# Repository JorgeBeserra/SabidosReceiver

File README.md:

# SabidosReceiver

Projeto de receptor e processador de áudio multicanal baseado no **PT2322-S**, com seletor **PT2323-S**, controlado por um **ESP32**.

## Ferramenta

O projeto principal está em formato **KiCad 10**:

- `SabidosReceiver.kicad_pro`
- `SabidosReceiver.kicad_sch`
- `SabidosReceiver.kicad_pcb`

Abra sempre o arquivo `SabidosReceiver.kicad_pro` para manter o esquemático e a PCB associados ao mesmo projeto.

## Situação da migração

O projeto foi renomeado de `SabVolAudio` para `SabidosReceiver`. Ainda existem arquivos e identificadores legados preservados no repositório para conferência durante a migração.

Antes de removê-los definitivamente, é necessário confirmar que todas as folhas hierárquicas e todos os componentes foram convertidos corretamente para o formato atual do KiCad.

## Cuidados antes da fabricação

1. Confirmar fisicamente o encapsulamento do PT2322-S e validar o footprint em escala 1:1.
2. Abrir e salvar todas as folhas hierárquicas no KiCad 10.
3. Executar o ERC no esquemático.
4. Atualizar a PCB a partir do esquemático e revisar cada inclusão ou remoção proposta.
5. Executar o DRC na PCB.
6. Conferir a região da antena do ESP32 e manter cobre afastado.
7. Conferir polaridade dos capacitores eletrolíticos e pinagem de todos os conectores.
8. Gerar novos Gerbers somente depois da validação.

## Organização recomendada

- Arquivos `.kicad_*`: fontes atuais do projeto.
- Bibliotecas locais: símbolos e footprints necessários para abrir o projeto em outro computador.
- Modelos 3D: devem usar caminhos relativos com `${KIPRJMOD}`.
- Gerbers, backups, netlists e preferências locais não devem ser versionados.

## Observação importante

Os arquivos legados não devem ser apagados sem comparação visual com o esquemático atual, porque algumas folhas convertidas aparecem vazias e podem ainda depender do conteúdo antigo.

## Integração PT2323

A revisão em desenvolvimento completa o seletor U3 e as quatro entradas estéreo. Veja [mudanças e validação](docs/PT2323_INTEGRACAO.md). O esquema foi atualizado; a PCB ainda precisa receber essas mudanças.

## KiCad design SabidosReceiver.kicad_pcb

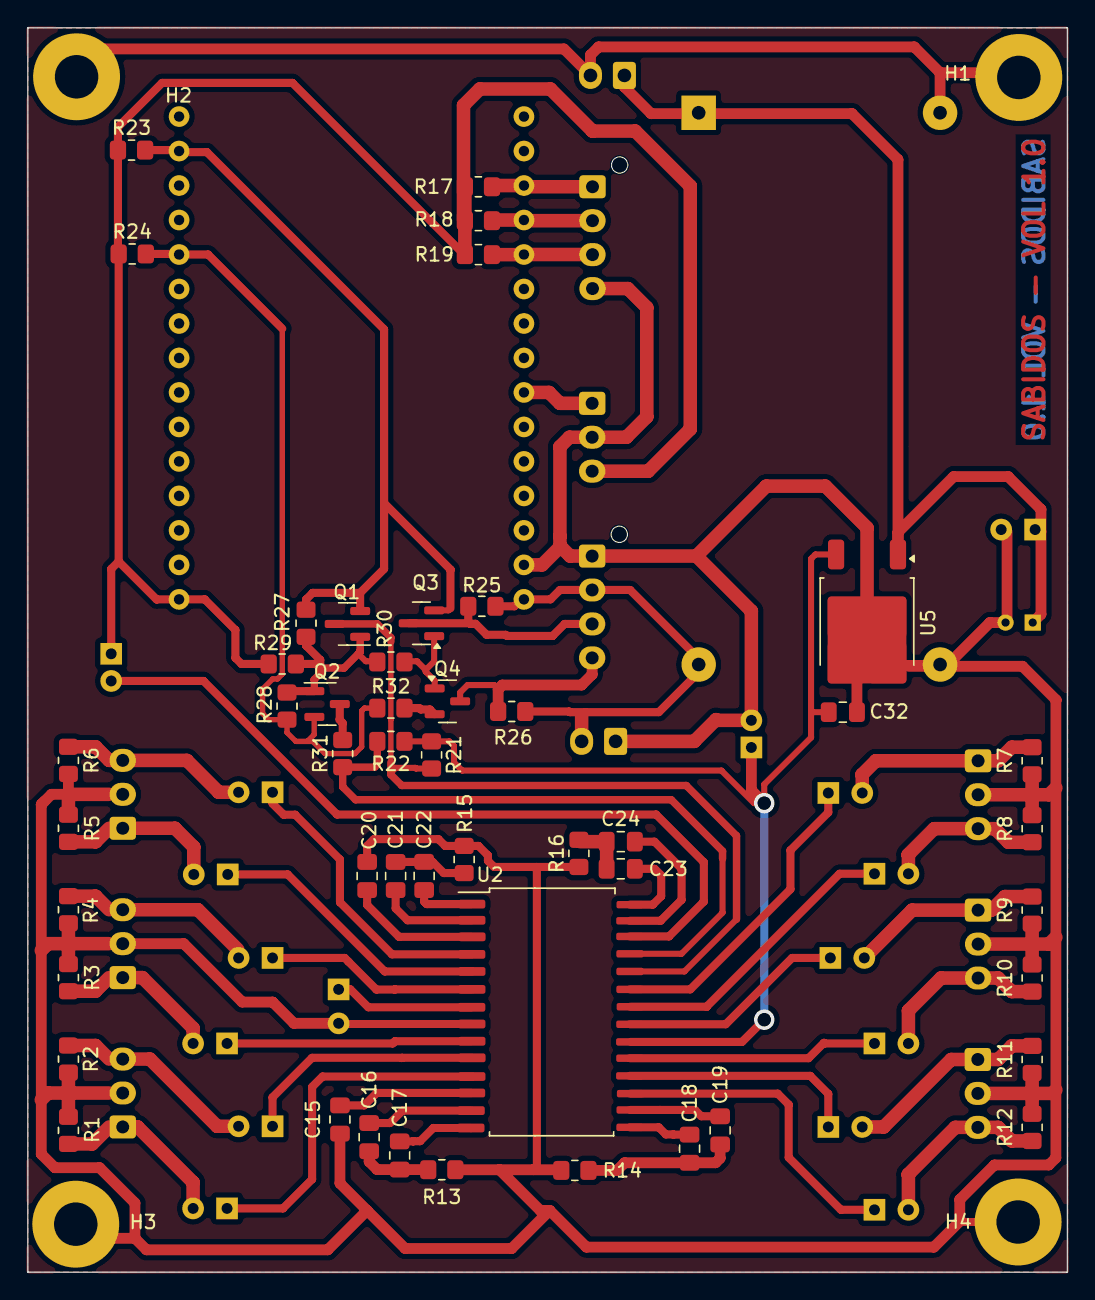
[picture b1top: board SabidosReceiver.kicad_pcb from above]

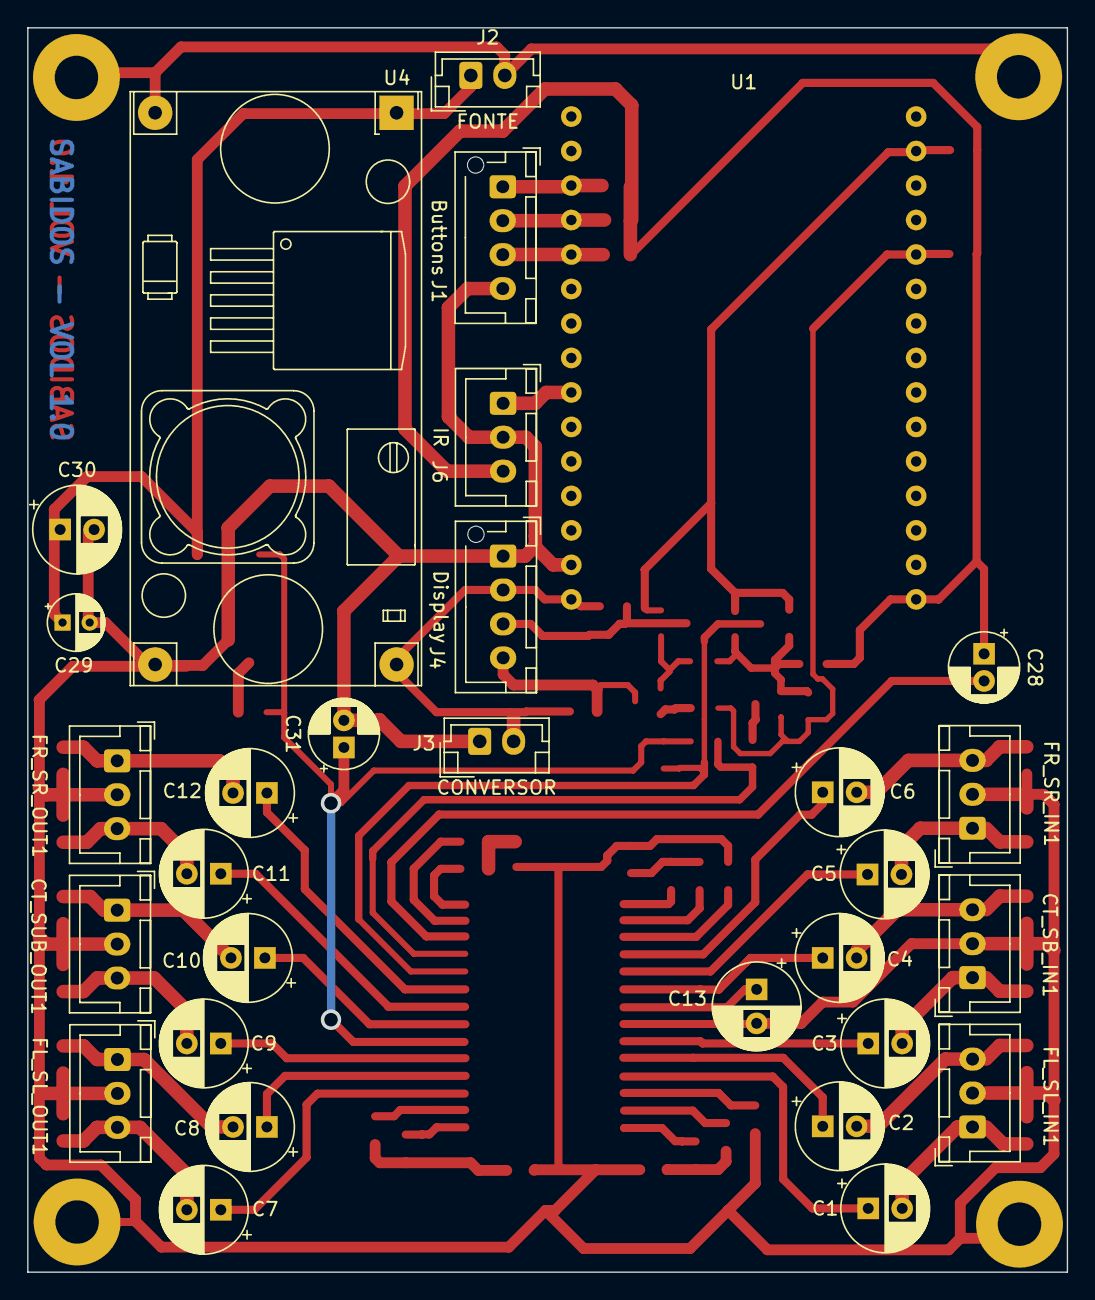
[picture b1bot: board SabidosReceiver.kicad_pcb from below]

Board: 2 copper layers, 76.6 x 91.7 mm, 82 parts (30 on the bottom side), 58 nets.

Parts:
C1, C2, C3, C4, C5, C6, C7, C8, C9, C10, C11, C12, C13: 10uF; CP_Radial_D6.3mm_P2.50mm
C15, C20: 2200pF; C_0805_2012Metric_Pad1.18x1.45mm_HandSolder
C16, C17, C21, C22: 0.01uF; C_0805_2012Metric_Pad1.18x1.45mm_HandSolder
C18, C19, C23, C24: 0.1uF; C_0805_2012Metric_Pad1.18x1.45mm_HandSolder
C28: 10MFD; CP_Radial_D5.0mm_P2.00mm
C29: 22uF; CP_Radial_D4.0mm_P2.00mm
C30: 100MFD; CP_Radial_D6.3mm_P2.50mm
C31: 22MFD; CP_Radial_D5.0mm_P2.00mm
C32: 0.1MFD; C_0805_2012Metric_Pad1.18x1.45mm_HandSolder
CT_SB_IN1: Conn_01x03_Pin; JST_XH_B3B-XH-A_1x03_P2.50mm_Vertical
CT_SUB_OUT1: Conn_01x03_Pin; JST_XH_B3B-XH-A_1x03_P2.50mm_Vertical
FL_SL_IN1: Conn_01x03_Pin; JST_XH_B3B-XH-A_1x03_P2.50mm_Vertical
FL_SL_OUT1: Conn_01x03_Pin; JST_XH_B3B-XH-A_1x03_P2.50mm_Vertical
FR_SR_IN1: Conn_01x03_Pin; JST_XH_B3B-XH-A_1x03_P2.50mm_Vertical
FR_SR_OUT1: Conn_01x03_Pin; JST_XH_B3B-XH-A_1x03_P2.50mm_Vertical
H1, H2, H3, H4: M3; MountingHole_3.2mm_M3_Pad
J1: Buttons; JST_XH_B4B-XH-AM_1x04_P2.50mm_Vertical
J2: FONTE; JST_EH_B2B-EH-A_1x02_P2.50mm_Vertical
J3: CONVERSOR; JST_EH_B2B-EH-A_1x02_P2.50mm_Vertical
J4: Display; JST_XH_B4B-XH-AM_1x04_P2.50mm_Vertical
J6: IR; JST_XH_B3B-XH-A_1x03_P2.50mm_Vertical
Q1, Q2, Q3, Q4: 2N7002; SOT-23
R1, R2, R3, R4, R5, R6, R7, R8, R9, R10, R11, R12: 100k; R_0805_2012Metric_Pad1.20x1.40mm_HandSolder
R13, R15: 3.3k; R_0805_2012Metric_Pad1.20x1.40mm_HandSolder
R14, R16: 6.2k; R_0805_2012Metric_Pad1.20x1.40mm_HandSolder
R17, R18, R21, R22, R23, R24, R25, R26, R27, R28: 10K; R_0805_2012Metric_Pad1.20x1.40mm_HandSolder
R19: 10K3; R_0805_2012Metric_Pad1.20x1.40mm_HandSolder
R29, R30, R31, R32: 0K; R_0805_2012Metric_Pad1.20x1.40mm_HandSolder
U1: DOIT-ESP32-DEVKIT-V1; ESP32-DOIT-DEVKIT
U2: PT2322-S; SOP-28_7.5x15.4mm_P1.27mm
U4: LM2596; YAAJ_DCDC_StepDown_LM2596
U5: LM78M08; TO-252-2

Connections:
+3V3: C28.1, J6.3, R17.1, R18.1, R19.1, R23.1, R24.1, R29.1, U1.16 (3V3)
+3V3-0: Q1.1 (G), Q2.1 (G), R27.1, R28.1, R29.2, R30.1
+3V3-1: Q3.1 (G), Q4.1 (G), R30.2
+5V: J3.2, J4.2, R25.1, R26.1, U1.15 (5V), U4.4 (Vout)
+8V: C31.1, C32.1, R21.1, R22.1, U2.20 (VCC), U5.3 (VO)
+12V: C29.1 (+), C30.1, J2.1, U4.1 (Vin), U5.1 (VI)
/Processador/SCL-HV-5V: J4.3, Q3.3 (D), R25.2
/Processador/SDA-HV-5V: J4.4, Q4.3 (D), R26.2
GNDD: C13.2 (-), C15.2, C20.1, C28.2, C29.2 (-), C30.2, C31.2, C32.2, CT_SB_IN1.2, CT_SUB_OUT1.2, FL_SL_IN1.2, FL_SL_OUT1.2, FR_SR_IN1.2, FR_SR_OUT1.2, H1.1, H2.1, H3.1, H4.1, J1.4, J2.2, J3.1, J4.1, J6.2, R1.2, R2.2, R3.2, R4.2, R5.2, R6.2, R7.2, R8.2, R9.2, R10.2, R11.2, R12.2, R13.2, R14.2, R15.1, R16.1, U1.14 (GND), U1.17 (GND), U2.8 (GND), U2.26 (DGND), U4.2 (GND), U4.3 (GND), U5.2 (GND)
GPIO26: J6.1, U1.9 (GPIO26_ADC2-CH9_DAC2_RTC-GPIO7)
unnamed: C1.1 (+), U2.11 (IN_FL)
unnamed: C1.2 (-), FL_SL_IN1.1, R1.1
unnamed: C2.1 (+), U2.10 (IN_SL)
unnamed: C2.2 (-), FL_SL_IN1.3, R2.1
unnamed: C3.1 (+), U2.9 (IN_CT)
unnamed: C3.2 (-), CT_SB_IN1.1, R3.1
unnamed: C4.1 (+), U2.6 (IN_SUB)
unnamed: C4.2 (-), CT_SB_IN1.3, R4.1
unnamed: C5.1 (+), U2.5 (IN_SR)
unnamed: C5.2 (-), FR_SR_IN1.1, R5.1
unnamed: C6.1 (+), U2.4 (IN_FR)
unnamed: C6.2 (-), FR_SR_IN1.3, R6.1
unnamed: C7.1 (+), U2.17 (OUT_FL)
unnamed: C7.2 (-), FL_SL_OUT1.3, R12.1
unnamed: C8.1 (+), U2.18 (OUT_SL)
unnamed: C8.2 (-), FL_SL_OUT1.1, R11.1
unnamed: C9.1 (+), U2.19 (OUT_CT)
unnamed: C9.2 (-), CT_SUB_OUT1.3, R10.1
unnamed: C10.1 (+), U2.21 (OUT_SUB)
unnamed: C10.2 (-), CT_SUB_OUT1.1, R9.1
unnamed: C11.1 (+), U2.22 (OUT_SR)
unnamed: C11.2 (-), FR_SR_OUT1.3, R8.1
unnamed: C12.1 (+), U2.23 (OUT_FR)
unnamed: C12.2 (-), FR_SR_OUT1.1, R7.1
unnamed: C13.1 (+), U2.7 (VREF)
unnamed: C16.2, C17.2, R13.1
unnamed: C18.2, C19.2, R14.1
unnamed: C21.1, C22.1, R15.2
unnamed: C23.1, C24.1, R16.2
unnamed: J1.1, R17.2, U1.3 (GPIO39_ADC1-CH3_SENS-VN_RTC-GPIO3)
unnamed: J1.2, R18.2, U1.4 (GPIO34_ADC1-CH6_RTC-GPIO4)
unnamed: J1.3, R19.2, U1.5 (GPIO35_ADC1-CH7_RTC-GPIO5)
unnamed: Q2.3 (D), R31.2
unnamed: Q4.2 (S), R32.1
unnamed: C15.1, U2.12 (CTRE_FL)
unnamed: C20.2, U2.3 (CTRE_FR)
unnamed: C18.1, U2.15 (RCBAS1_FL)
unnamed: C23.2, U2.28 (RCBAS1_FR)
unnamed: C19.1, U2.16 (RCBAS2_FL)
unnamed: C24.2, U2.27 (RCBAS2_FR)
unnamed: C21.2, U2.2 (RCMID1)
unnamed: C16.1, U2.13 (RCMID1_FL)
unnamed: C22.2, U2.1 (RCMID2)
unnamed: C17.1, U2.14 (RCMID2_FL)
SCL-3V: Q1.2 (S), Q3.2 (S), R23.2, R27.2, U1.29 (GPIO22_I2C-SCL)
SCL-HV-8V: Q1.3 (D), R21.2, U2.24 (SCL)
SDA-3V: Q2.2 (S), R24.2, R28.2, R32.2, U1.26 (GPIO21_I2C-SDA)
SDA-HV-8V: R22.2, R31.1, U2.25 (SDA)
